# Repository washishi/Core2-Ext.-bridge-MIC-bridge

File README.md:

# Core2-Ext. bridge & MIC bridge

## 概要
主にRT版ｽﾀｯｸﾁｬﾝにおいて利用できる下記基板(フレキシブル基板)のKiCad7.0で作成したデータです  
(すぐに[JLCPCB](https://jlcpcb.com/JPV)へ製造を依頼できるGarberFile [Core2_Ext._bridge.zip](./production/Core2_Ext._bridge_2023-09-26_04-28-21/Core2_Ext._bridge.zip) もあります)

* Core2-Ext. brige
  * [M5Core2](https://docs.m5stack.com/ja/core/core2) の CORE2 Expansion board を接続してマイクとIMUが使える様にします(はんだ付け不要)  
  * CORE2専用です (BASIC系では取り付けたCORE2 Expansion boardが物理的に干渉するため利用できません)  
  * ｽﾀｯｸﾁｬﾝ基板以外でも物理的に干渉しなければ使えると思います
  
* MIC brige
  * CORE S3以外のM5Stackを利用する場合にPDMマイクを内蔵で追加します
  * ｽﾀｯｸﾁｬﾝ基板以外でも物理的に干渉しなければ使えると思います
  * マイクの接続先のGPIOはCORE2(for AWSも含む)と同じで下記になります  
  　MIC CLK：GPIO0  
  　MIC DAT：GPIO34  
    ※BASIC系で利用する場合はPORT-AにPDMマイクユニットを接続する場合とはGPIOが異なりますのでソースを変更してリコンパイルをする必要があります

  * 利用できることを確認しているマイクは[秋月電子](https://akizukidenshi.com/catalog/)で扱っている下記のどちらかになります  
  (店舗在庫はあまりたくさん置いてないことがあるので通販で購入するか行く場合は事前にWebで在庫数確認したほうがいいかも)
    * SPH0641LU4H使用 超広帯域マイクモジュールキット  
      通販コード：K-15577  
      (クランプで挟みはんだ付け不要で取り付け または はんだ付けにより取り付け)  
    * 超小型シリコンマイクロホン 超音波対応 SPH0641LU4H-1-8  
      通販コード：P-14730    
      (マイクチップ単体、リフローによるはんだ付けが必要)  
      ※その他[Knowles社のサイズ、端子が同じデジタルPMD出力のマイク](https://www.knowles.com/subdepartment/dpt-microphones/subdpt-sisonic-surface-mount-mems)はおそらく使えるのではないかと思われます

## 注意事項等(重要)
 * 無保証です、自己責任で利用願います  
  本データおよび本データから作成したフレキシブル基板の利用上等に発生したいかなる問題についても私の方では補償いたしません
 * 取り付けてそのままでも問題ないことを確認していますがショート等が気になる場合は各自テープを貼ったりして絶縁してください  
 * 一度取り付けたフレキシブル基板は取り外すとスルーホールが広がってしまう為 
   再度取り付けても接触不良が発生して利用できない場合が多いです (シール等と同じと考えてください)  
   また 初回取り付けでも個体差等により接触不良を起こす場合があるかもしれません

## ライセンス
   このリポジトリ配下のファイルは[Apache version 2.0ライセンス](./LICENSE)で配布いたします  
   改変、頒布等 は自由にしていただいて構いません

<br>

## JLCPCBへの製造の依頼について
費用は円のレートにより変動しますが最低の送料込みで概ね2,500円弱で5枚のフレキシブル基板が作れます

※下記に簡単に手順を書きますが 画像付きで説明されているサイト等もあるので各自検索してみてください
* ユーザ登録、配送先の登録について
   * まずユーザ登録が必要です、まだの場合は[JLCPCBのWeb](https://jlcpcb.com/JPV)を開き右上の「登録」よりユーザ登録を行います  
    登録方法についてはユーザ名、メールアドレス、パスワード(確認を含め2回)の入力し「I'm not a robot」のチェックボックスをつけて「Sign Up」をクリックするか 「Sign in with google」をクリックしてGoogleアカウント連携を行います  
   * JLCPCBより登録確認のメールが指定したメールアドレスまたはgoogleアカウントのgmailに届くので  
   メールにある「Verify email address」のリンクを開くと登録完了となります
   * 再度[JLCPCBのWeb](https://jlcpcb.com/JPV)を開き右上の今度は「ログイン」を選び必要事項を入力して「Sign In」をクリックするか  
   Sign in with google」をクリックして連携したGoogleアカウントでログインします
   * ログインしたら右上に自分のユーザ名が出ているのでクリックします
   * 右上の「Ship to」」をクリックして「Country/Region」(国:Japan) と「Currency」(通貨:JPY￥)を設定します  
   * 左側の一覧より「Account Setting」をクリックしますその後「Address Book」の項目の右のほうにある「Edit」をクリックします  
   すると「Address Book」が開くので、「+ Add a new shipping address」をクリックして送付先の氏名や住所等を入力して「SAVE」をクリックして保存します   

      以上でユーザ登録及び配送先の登録は完了です
* JLCPCBへの製造の依頼方法
   * まずGarberFile [Core2_Ext._bridge.zip](./production/Core2_Ext._bridge_2023-09-26_04-28-21/Core2_Ext._bridge.zip) をダウンロードして任意の場所に保存します
   *  [JLCPCBのWeb](https://jlcpcb.com/JPV)を開きログインします
   * ログインしたら右上に自分のユーザ名をクリックし、その後「Order now」をクリックします
   * するとオーダーの詳細画面になるので一番上の選択が「Standard PCB/PCBA」になっていることを確認します
   * 「Add gerber file」をクリックして先ほどダウンロードしたGarberFile  [Core2_Ext._bridge.zip](./production/Core2_Ext._bridge_2023-09-26_04-28-21/Core2_Ext._bridge.zip) を選びアップロードします(すると基板の図が表示されます)
   * 詳細より下記を変更等します　 変更内容によっては右側の「Calculated Price」(製造費用)が変動します
        * Base Material ： 「**Flex**」 (フレキシブル基板) を選択
        * PCB Qty ： 製造する数量です デフォルトは5枚ですが5枚を選ぶと6枚届くことが多いです (製造の際に四角にならないと面倒な為？)
        * 今回のデータは1枚で Core2-Ext. brigeを2枚、MIC Bridgeを1枚含んだ基板のデータとなっています(個々の切断は行わないので「Different Design」や「Delivery Format」はデフォルトで構いません 出来上がり後各自カッターやはさみで切断してください)
        * Remove Order Number ： 「**Specific location**」 製造時に基板に追加されるオーダー番号をあらかじめキーワードで指定した位置(未使用部分の一部を指定)にします

     その他はデフォルトで問題ありません　(色とかは好みで変更してもかまいませんが追加費用が発生します)  
      問題がなければ右側の「SAVE TO CART」をクリックしてカートに登録します
   * カートに登録したら右上のカートのアイコンをクリックして開きます  
   * カートの内容が表示されるので問題なければ右側の「Secure Checkout」をクリックして進みます
    * 「1.Shipping Address」で「Shipping Information」(配送先)と「Billing Information」(請求情報のメールの送付先)確認が出るので問題なければ 「Continue」で進みます
    * 「2.Shipping Method」(配送方法の選択)になります、しっかりした梱包で発送されるので特に急がないのであれば一番安い「OCS NEP」でいいと思います (選択により右の「Shipping」(送料)及び「Grand Total」(総合計価格)が変わります)
  　選択したら「Continue」で次に進みます
    * 「3.Submit Order」支払タイミングの選択です デフォルトの「Pay Directly(recommended)」(即時)でいいと思います、「Continue」で次に進みます
    * 「4.Payment」 支払方法の選択です　PayPal または クレジットカードが選べるので好きなほうを選びます (PayPalを利用する場合は[PayPalの登録](https://www.paypal.com/jp/webapps/mpp/account-selection)が必要です)  
    またここで利用可能なクーポンがある場合はクーポンの選択が出ますので利用する場合は選びます(新規登録した場合は総額54$の各種クーポンが貰えてるはずです、クーポンは利用期限がありまた3Dプリントのクーポンもあると思うので別途ｽﾀｯｸﾁｬﾝの外装等を注文してみてもいいかも)  
    問題なければ 「Pay」をクリックして発注を確定します 支払いでPayPalを選んだ場合はPayPalの画面が別に開くのでそこで確認すると発注確定となります  
    後は待てばそのうち製造されたフレキシブル基板が届きます。(製造、発送の状況は「Order History」から確認できます)  
    配送方法が「OCS NEP」の場合は日本に着いてからはヤマト運輸でサイズが小さいためネコポスでポストに配達されることが多い様です

## 組立/取り付け方法等
* Core2-Ext. brige
  * CORE2(無印)付属のCORE2 Expansion boardを取り付けるものです (※CORE2 Expansion boardのみの別売りはありません)   
  * CORE2 Expansion board に Core2-Ext. brige を写真の向きで合わせて定規等でできるだけ水平状態のまま奥まで押し込みます  
    (この写真ではCore2-Ext. brigeの向きはCORE2 Expansion boardの文字の向きに合わせていますが　Core2-Ext. brigeのパターン的には逆さにしても裏返しても問題ないように作ってあります)
    
   * 繋げたものをさらにｽﾀｯｸﾁｬﾝ基板のピンヘッダに合わせて同様に定規等で奥まで押し込みます(ケースに基板が付いた状態で押し込みにくい場合はピンヘッダに合わせて置いてそのままずれないように注意しながらCORE2を上からはめてしまってもかまいません)  
   * 後は通常通りCORE2を取り付ければCORE2 Expansion boardのマイク/IMUが利用できるはずです (CORE2のファクトリーデモ等で確認してみてください)  
    
<br>  

* MIC brige  
  * BASIC系やCORE2を利用する際に追加でPDMマイクを取り付けるものです
  * はんだ付けなしで利用する場合
    * MIC brige以外に必要な物  
      * [秋月電子](https://akizukidenshi.com/catalog/)で扱っている
        SPH0641LU4H使用 超広帯域マイクモジュールキット  
        通販コード：K-15577  
      * タミヤの 楽しい工作シリーズ（クラフト）No.202 (Item No:70202)  
        [プラ材3mmコの字形棒（5本入）](https://www.tamiya.com/japan/products/70202/index.html)  
        ※透明のもありますが材質的に白のほうが加工しやすい様です   
        10mmで切断してフレキを基板に挟むクランプとして使います  
        (少量しか使わないので３Dプリンタで作成したり他の代用品を探してみてもいいかも)  

    * 取り付け  
      * MIC brigeとマイクモジュールの端子を接触するように合わせマイクモジュールを巻き込むようにしてマイクモジュール付属の細ピンヘッダを穴に刺して仮止めします(穴が小さめなので少し力をかけて押し込んでください)  
        
      * コの字形プラ棒のクランプを差し込みます   
        
      * 仮止めのピンヘッダを取り外しクランプを奥まで押し込みます 
        
      * 後はｽﾀｯｸﾁｬﾝ基板のピンヘッダに合わせて定規等でできるだけ水平状態のまま押し込めば完成です(押し込みにくい場合はピンヘッダに合わせてフレキを置いて、ずれないように注意しながらそのままM5Coreを取り付けてください)  
        
      * 完成  
        
  * はんだ付けして利用する場合  
    * MIC brige以外に必要な物は下記です  
      * [秋月電子](https://akizukidenshi.com/catalog/)で扱っている
        SPH0641LU4H使用 超広帯域マイクモジュールキット  
        通販コード：K-15577  
      * はんだごて、はんだ、ニッパー、ラジオペンチ(ピンヘッダを利用する場合) 等
     * マイクユニット付属のピンヘッダを利用する場合　
       * まずマイクユニットのマイクの穴の方にピンが出る状態でピンヘッダをはんだ付けします(通常利用する場合と逆にピンが出る状態)
       * その後ピンヘッダの黒い樹脂をラジオペンチ等で引き抜きます(そのまま利用するとBASIC系では背が高くなり干渉するので黒い樹脂を外してフレキとモジュールを密着させます) 
       * ピンヘッダのピンのついたマイクモジュールをフレキに刺してモジュールの基板とフレキが密着した状態ではんだだ付けします(ピンヘッダを刺す穴が小さめなので少し力をかけて押し込んでください)      
        * はんだ付け後ピンヘッダの飛び出した部分はニッパーでカットしてください
     * マイクユニット付属のピンヘッダを利用しない場合　
       * マイクユニットとフレキのランドに薄く予備はんだします
       * マイクユニットをフレキに合わせ角からはんだごてを当ててはんだを追加し両方のはんだを溶かして接続します  
       * あとははんだ付けしない場合と同様に取り付けます  
        <p align="center"> 

        </p>  
         ※上の写真では余白に書いたｽﾀｯｸﾁｬﾝの絵の部分を切り取らずにそのまま残してます  

  * マイクチップをリフローして取り付ける方法  
   ※以下の写真のフレキは旧バージョンでマイクの向き、パターン等が異なりますが制作方法は同様です
    * MIC brige以外に必要な物  
      * [秋月電子](https://akizukidenshi.com/catalog/)で扱っている
         超小型シリコンマイクロホン 超音波対応 SPH0641LU4H-1-8  
        通販コード：P-14730  
      * ヒートテーブル、クリームはんだ、ピンセット等  
        <p align="center"> 
        
    * リフロー手順  
      * ごく少量クリームはんだをマイクチップのランドに塗ります    
       ※写真の量だとクリームはんだが多すぎた様です   
        
      * ピンセットでマイクチップを載せます  
        その後ヒートテーブルで加熱してリフローします  
        (私の方では融点138℃の低温クリームはんだを使ったので150℃で10秒ほど加熱しました)
        
      * リフロー後多すぎたクリームはんだがはんだボールになってしまいました・・・  
        ピンセットの先等で擦って取れる範囲で取り除きます   
        
      * はんだボール除去後   
        
      * 後はｽﾀｯｸﾁｬﾝ基板のピンヘッダに刺して完成です  
        フレキの左側は不要なので切ってしまってもかまいません (今回配布するデータはマイクの端で切ってしまっても問題ない様にパターンが作ってあります)    
        <p align="center"> 
          
        </p>
        <br>  
        <br>  
## スルーホールでピンヘッダに接続する仕組みについて
  ピンヘッダのピンは1辺0.8mmの角型になっています、その為対角では約0.83mmとなるので  
  0.8mmのスルーホールに刺すことにより4つの角がスルーホールを広げて接触します  
  ただし一度取り外すと穴が広がって接触不良となりやすいので再利用は難しいです

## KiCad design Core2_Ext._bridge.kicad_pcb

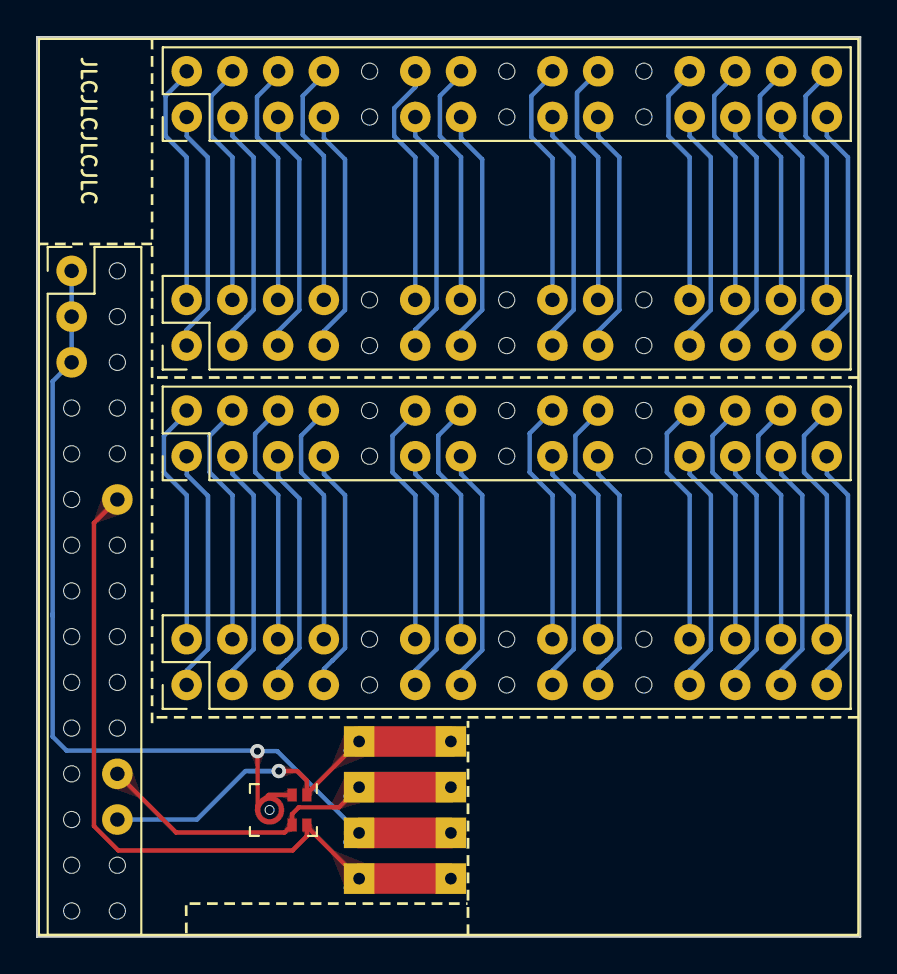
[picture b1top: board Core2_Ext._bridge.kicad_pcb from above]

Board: 2 copper layers, 45.8 x 50.0 mm, 8 parts (0 on the bottom side), 52 nets.

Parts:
J1, J2, J3, J4, J5: Conn_02x15_Odd_Even; PinHeader_2x15_P2.54mm_Vertical
J6, J7: Conn_01x04; PinHeader_1x04_P2.54mm_Vertical
MIC: SPH0641LM4H-1; Knowles_LGA-5_3.5x2.65mm

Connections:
+3.3V: J5.12, J6.1, J7.1, MIC.5 (VDD)
GND: J5.1, J5.3, J5.5, J6.2, J7.2, MIC.2 (SEL), MIC.3 (GND)
unnamed: J1.1, J2.1
unnamed: J1.2, J2.2
unnamed: J1.3, J2.3
unnamed: J1.4, J2.4
unnamed: J1.5, J2.5
unnamed: J1.6, J2.6
unnamed: J1.7, J2.7
unnamed: J1.8, J2.8
unnamed: J1.11, J2.11
unnamed: J1.12, J2.12
unnamed: J1.13, J2.13
unnamed: J1.14, J2.14
unnamed: J1.17, J2.17
unnamed: J1.18, J2.18
unnamed: J1.19, J2.19
unnamed: J1.20, J2.20
unnamed: J1.23, J2.23
unnamed: J1.24, J2.24
unnamed: J1.25, J2.25
unnamed: J1.26, J2.26
unnamed: J1.27, J2.27
unnamed: J1.28, J2.28
unnamed: J1.29, J2.29
unnamed: J1.30, J2.30
unnamed: J3.1, J4.1
unnamed: J3.2, J4.2
unnamed: J3.3, J4.3
unnamed: J3.4, J4.4
unnamed: J3.5, J4.5
unnamed: J3.6, J4.6
unnamed: J3.7, J4.7
unnamed: J3.8, J4.8
unnamed: J3.11, J4.11
unnamed: J3.12, J4.12
unnamed: J3.13, J4.13
unnamed: J3.14, J4.14
unnamed: J3.17, J4.17
unnamed: J3.18, J4.18
unnamed: J3.19, J4.19
unnamed: J3.20, J4.20
unnamed: J3.23, J4.23
unnamed: J3.24, J4.24
unnamed: J3.25, J4.25
unnamed: J3.26, J4.26
unnamed: J3.27, J4.27
unnamed: J3.28, J4.28
unnamed: J3.29, J4.29
unnamed: J3.30, J4.30
unnamed: J5.24, J6.3, J7.3, MIC.4 (CLOCK)
unnamed: J5.26, J6.4, J7.4, MIC.1 (DATA)

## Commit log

2023-10-20 [add]新規追加、公開
2023-10-20 イメージ修正
2023-10-20 [fix]フォーマット崩れ等を修正
